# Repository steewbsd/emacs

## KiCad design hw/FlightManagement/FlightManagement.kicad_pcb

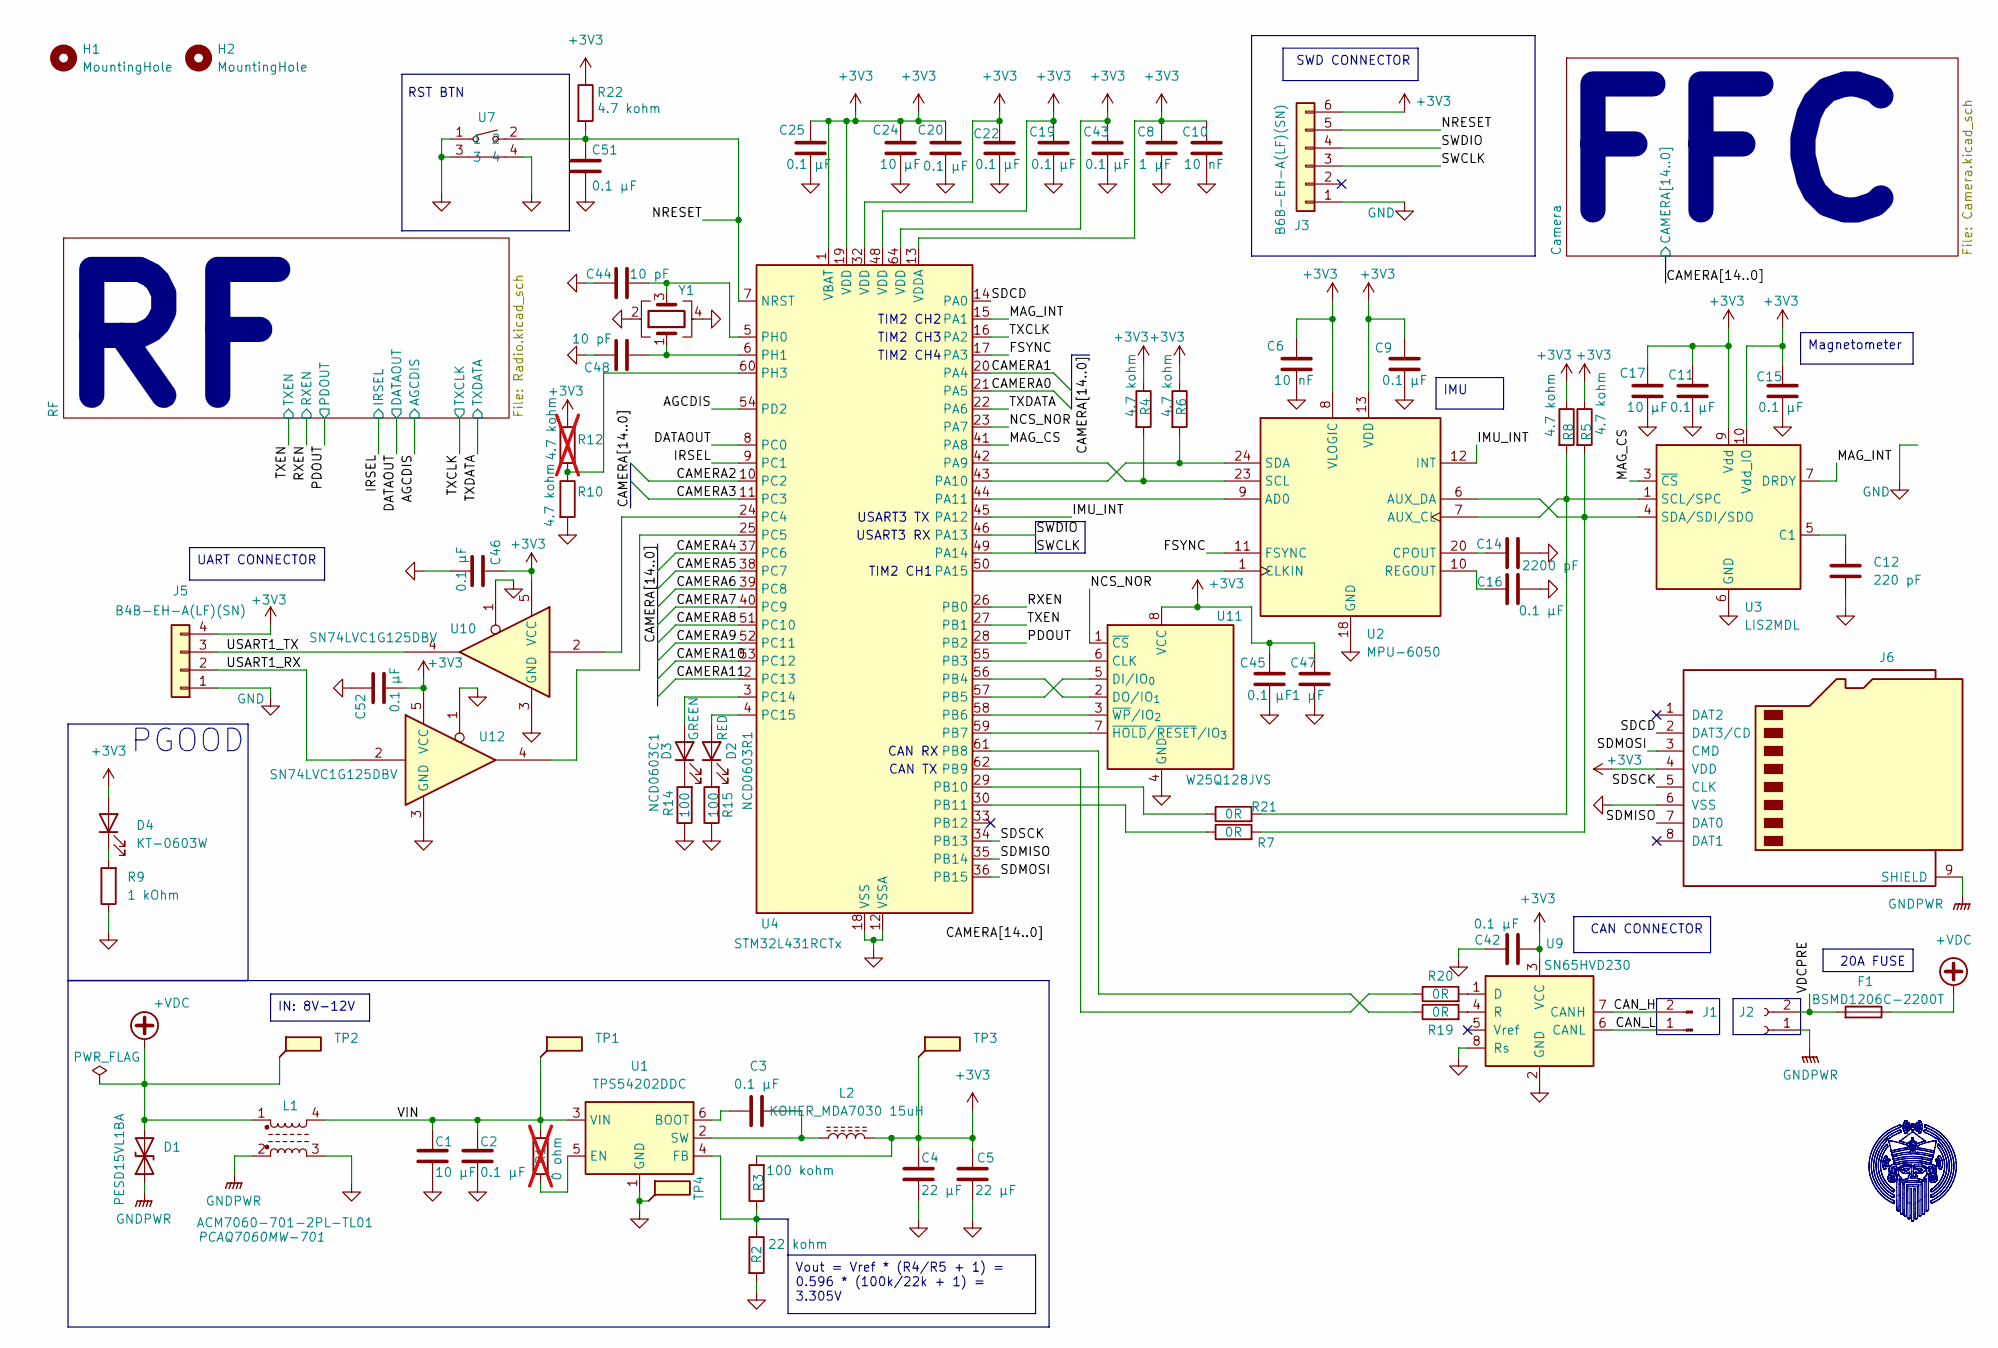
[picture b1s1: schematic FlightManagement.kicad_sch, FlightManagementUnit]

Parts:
C1, C17, C24: 10 µF; C_0603_1608Metric_Pad1.08x0.95mm_HandSolder; Rated Voltage 16V; Tolerance 10%
C2, C3, C9, C11, C15, C16, C19, C20, C22, C25, C42, C43, C45, C46, C51, C52: 0.1 µF; C_0603_1608Metric_Pad1.08x0.95mm_HandSolder; Rated Voltage 50V; Tolerance 10%
C4, C5: 22 µF; C_0603_1608Metric_Pad1.08x0.95mm_HandSolder; Rated Voltage 16V; Tolerance 20%
C6, C10: 10 nF; C_0603_1608Metric_Pad1.08x0.95mm_HandSolder; Rated Voltage 50V; Tolerance 10%
C8, C47: 1 µF; C_0603_1608Metric_Pad1.08x0.95mm_HandSolder; Rated Voltage 25V; Tolerance 10%
C12: 220 pF; C_0603_1608Metric_Pad1.08x0.95mm_HandSolder
C14: 2200 pF; C_0603_1608Metric_Pad1.08x0.95mm_HandSolder
C44, C48: 10 pF; C_0603_1608Metric_Pad1.08x0.95mm_HandSolder; Rated Voltage 50V; Tolerance 0.25pF
D1: PESD15VL1BA; D_SOD-323_HandSoldering
D2: RED; LED_0603_1608Metric
D3: GREEN; LED_0603_1608Metric
D4: KT-0603W; LED_0603_1608Metric_Pad1.05x0.95mm_HandSolder
F1: BSMD1206C-2200T; Fuse_1206_3216Metric_Pad1.42x1.75mm_HandSolder
H1, H2: MountingHole; MountingHole_2.2mm_M2
J1: Conn_01x02_Pin; JST_XH_B2B-XH-A_1x02_P2.50mm_Vertical
J2: Conn_01x02_Socket; JST_VL_B02P-VL_1x02_P6.2mm_Vertical
J3: B6B-EH-A(LF)(SN); JST_EH_B6B-EH-A_1x06_P2.50mm_Vertical
J5: B4B-EH-A(LF)(SN); JST_EH_B4B-EH-A_1x04_P2.50mm_Vertical
J6: Micro_SD_Card; microSD_HC_Molex_47219-2001
L1: L_Ferrite_Coupled_1423; L_CommonModeChoke_TDK_ACM7060
L2: KOHER_MDA7030 15uH; L_KOHERelec_MDA7030
R1: 0 ohm; R_0603_1608Metric_Pad0.98x0.95mm_HandSolder; Tolerance Jumper; not fitted
R2: 22 kohm; R_0603_1608Metric_Pad0.98x0.95mm_HandSolder; Tolerance 1%
R3: 100 kohm; R_0603_1608Metric_Pad0.98x0.95mm_HandSolder; Tolerance 1%
R4, R5, R6, R8, R10, R22: 4.7 kohm; R_0603_1608Metric_Pad0.98x0.95mm_HandSolder; Tolerance 1%
R7, R19, R20, R21: 0R; R_0603_1608Metric_Pad0.98x0.95mm_HandSolder
R9: 1 kOhm; R_0603_1608Metric_Pad0.98x0.95mm_HandSolder
R12: 4.7 kohm; R_0603_1608Metric_Pad0.98x0.95mm_HandSolder; Tolerance 1%; not fitted
R14, R15: 100; R_0603_1608Metric
TP1, TP2, TP3, TP4: TestPoint_Flag; TestPoint_Pad_1.0x1.0mm
U1: TPS54202DDC; SOT-23-6_Handsoldering
U2: MPU-6050; InvenSense_QFN-24_4x4mm_P0.5mm
U3: LIS2MDL; LGA-12_2x2mm_P0.5mm
U4: STM32L431RCTx; LQFP-64_10x10mm_P0.5mm
U7: YTS1C0033BBG01; SW-SMD_YIYUAN_YTS1C003XXX; LCSC Part C5188566
U9: SN65HVD230; SOIC-8_3.9x4.9mm_P1.27mm
U10, U12: SN74LVC1G125DBV; SOT-23-5_HandSoldering
U11: W25Q128JVS; SOIC-8_5.3x5.3mm_P1.27mm
Y1: Crystal_GND24; Crystal_SMD_3225-4Pin_3.2x2.5mm_HandSoldering

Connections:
+3V3: C4.1, C5.1, C6.2, C8.2, C9.2, C10.2, C11.2, C15.2, C17.1, C19.2, C20.2, C22.2, C24.1, C25.2, C42.1, C43.2, C45.2, C46.2, C47.2, C52.1, D4.2 (A), J3.6, J5.4, J6.4 (VDD), L2.2, R3.2, R4.1, R5.1, R6.1, R8.1, R12.1, R22.1, TP3.1, U2.8 (VLOGIC), U2.13 (VDD), U3.9 (Vdd), U3.10 (Vdd_IO), U4.1 (VBAT), U4.9 (PC1), U4.13 (VDDA), U4.19 (VDD), U4.32 (VDD), U4.48 (VDD), U4.64 (VDD), U9.3 (VCC), U10.5 (VCC), U11.8 (VCC), U12.5 (VCC); also elsewhere on the board
+VDC: D1.2 (A2), F1.1, L1.1, TP2.1
/AGCDIS: U4.54 (PD2); also elsewhere on the board
/CAMERA0: U4.21 (PA5)
/CAMERA1: U4.20 (PA4)
/CAMERA2: U4.10 (PC2)
/CAMERA3: U4.11 (PC3)
/CAMERA4: U4.37 (PC6)
/CAMERA5: U4.38 (PC7)
/CAMERA6: U4.39 (PC8)
/CAMERA7: U4.40 (PC9)
/CAMERA8: U4.51 (PC10)
/CAMERA9: U4.52 (PC11)
/CAMERA10: U4.53 (PC12)
/CAMERA11: U4.2 (PC13)
/CAN_H: J1.2, U9.7 (CANH)
/CAN_L: J1.1, U9.6 (CANL)
/DATAOUT: U4.8 (PC0); also elsewhere on the board
/FSYNC: U2.11 (FSYNC), U4.17 (PA3)
/IMU_INT: U2.12 (INT), U4.45 (PA12)
/MAG_CS: U3.3 (~CS), U4.41 (PA8)
/MAG_INT: U3.7 (DRDY), U4.15 (PA1)
/NCS_NOR: U4.23 (PA7), U11.1 (~CS)
/NRESET: C51.1, J3.5, R22.2, U4.7 (NRST), U7.2
/PDOUT: U4.28 (PB2); also elsewhere on the board
/RXEN: U4.26 (PB0); also elsewhere on the board
/SDCD: J6.2 (DAT3/CD), U4.14 (PA0)
/SDMISO: J6.7 (DAT0), U4.35 (PB14)
/SDMOSI: J6.3 (CMD), U4.36 (PB15)
/SDSCK: J6.5 (CLK), U4.34 (PB13)
/SWCLK: J3.3, U4.49 (PA14)
/SWDIO: J3.4, U4.46 (PA13)
/TXCLK: U4.16 (PA2); also elsewhere on the board
/TXDATA: U4.22 (PA6); also elsewhere on the board
/TXEN: U4.27 (PB1); also elsewhere on the board
/USART1_RX: J5.2, U12.2
/USART1_TX: J5.3, U10.4
/VDCPRE: F1.2, J2.2
/VIN: C1.1, C2.1, L1.4, R1.1, TP1.1, U1.3 (VIN)
GND: C1.2, C2.2, C4.2, C5.2, C6.1, C8.1, C9.1, C10.1, C11.1, C12.2, C14.2, C15.1, C16.1, C17.2, C19.1, C20.1, C22.1, C24.2, C25.1, C42.2, C43.1, C44.1, C45.1, C46.1, C47.1, C48.1, C51.2, C52.2, J3.1, J5.1, J6.6 (VSS), L1.3, R2.2, R9.1, R10.2, R14.1, R15.1, TP4.1, U1.1 (GND), U2.18 (GND), U3.6 (GND), U3.8 (GND), U4.12 (VSSA), U4.18 (VSS), U4.31 (VSS), U4.47 (VSS), U4.63 (VSS), U7.1, U7.3, U7.4, U9.2 (GND), U9.8 (Rs), U10.1, U10.3 (GND), U11.4 (GND), U12.1, U12.3 (GND), Y1.2, Y1.4; also elsewhere on the board
GNDPWR: D1.1 (A1), J2.1, J6.9 (SHIELD), L1.2
unnamed: D2.2 (A), U4.4 (PC15)
unnamed: D2.1 (K), R15.2
unnamed: D3.2 (A), U4.3 (PC14)
unnamed: D3.1 (K), R14.2
unnamed: D4.1 (K), R9.2
unnamed: R4.2, U2.23 (SCL), U4.42 (PA9)
unnamed: R6.2, U2.24 (SDA), U4.43 (PA10)
unnamed: U2.9 (AD0), U4.44 (PA11)
unnamed: U2.1 (CLKIN), U4.50 (PA15)
unnamed: U4.55 (PB3), U11.6 (CLK)
unnamed: U4.56 (PB4), U11.2 (DO/IO_{1})
unnamed: U4.57 (PB5), U11.5 (DI/IO_{0})
unnamed: U4.58 (PB6), U11.3 (~WP/IO_{2})
unnamed: U4.59 (PB7), U11.7 (~HOLD/~RESET/IO_{3})
unnamed: R19.1, U4.61 (PB8)
unnamed: R20.1, U4.62 (PB9)
unnamed: R21.1, U4.29 (PB10)
unnamed: R7.1, U4.30 (PB11)
unnamed: U4.24 (PC4), U10.2
unnamed: U4.25 (PC5), U12.4
unnamed: C44.2, U4.5 (PH0), Y1.3
unnamed: C48.2, U4.6 (PH1), Y1.1
unnamed: R10.1, R12.2, U4.60 (PH3)
unnamed: R8.2, R21.2, U2.7 (AUX_CL), U3.1 (SCL/SPC)
unnamed: R5.2, R7.2, U2.6 (AUX_DA), U3.4 (SDA/SDI/SDO)
unnamed: C14.1, U2.20 (CPOUT)
unnamed: C16.2, U2.10 (REGOUT)
unnamed: C12.1, U3.5 (C1)
unnamed: R20.2, U9.1 (D)
unnamed: R19.2, U9.4 (R)
unnamed: C3.1, U1.6 (BOOT)
unnamed: R1.2, U1.5 (EN)
unnamed: R2.1, R3.1, U1.4 (FB)
unnamed: C3.2, L2.1, U1.2 (SW)

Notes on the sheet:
USART3 RX
FFC
RST BTN
PGOOD
TIM2 CH2
USART3 TX
TIM2 CH3
TIM2 CH1
CAN TX
CAN RX
TIM2 CH4
Vout = Vref * (R4/R5 + 1) = 0.596 * (100k/22k + 1) = 3.305V
Magnetometer
IMU
SWD CONNECTOR
UART CONNECTOR
IN: 8V-12V
20A FUSE
CAN CONNECTOR

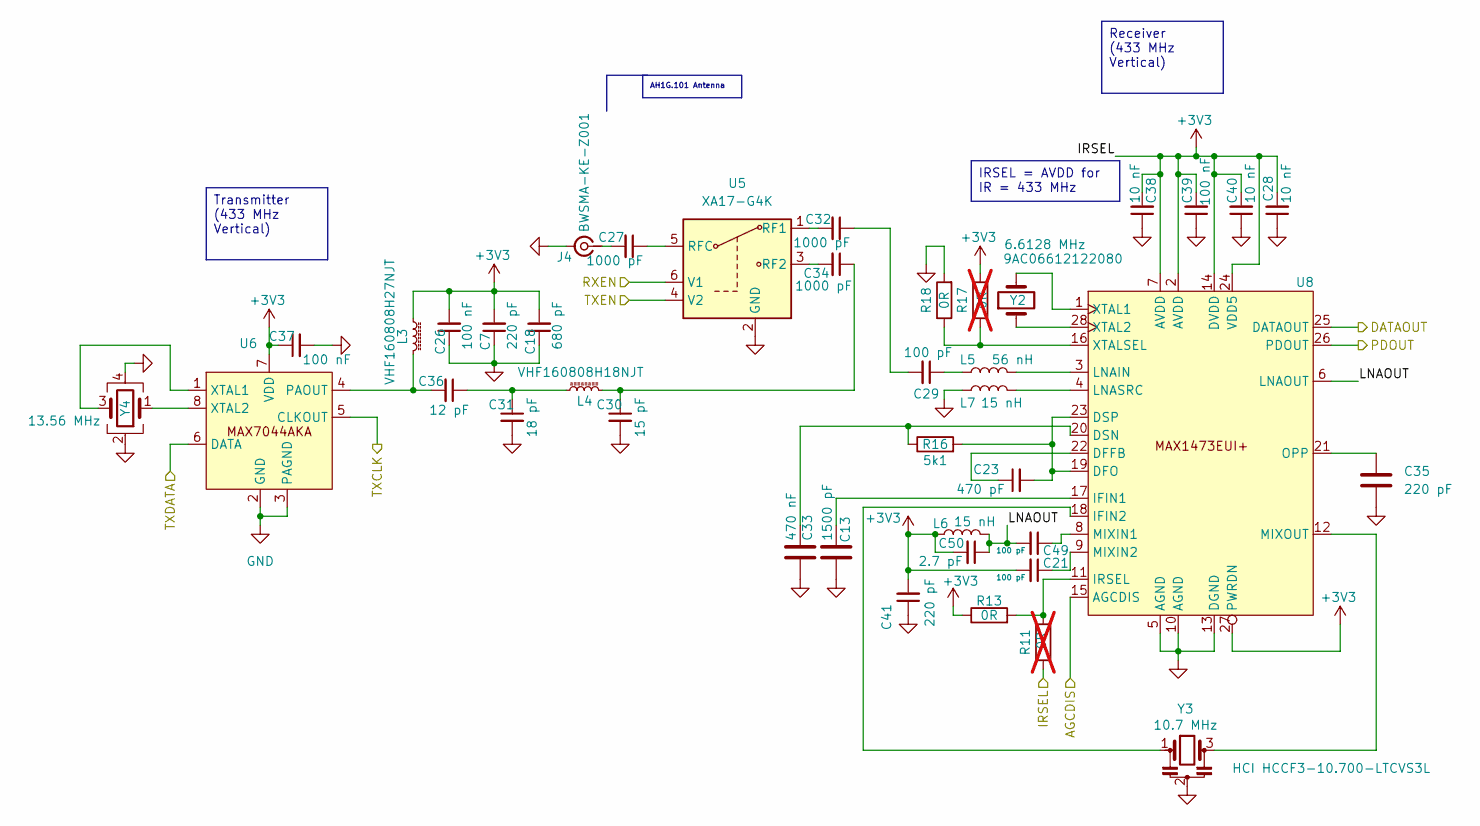
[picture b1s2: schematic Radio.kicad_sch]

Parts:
C7, C35, C41: 220 pF; C_0603_1608Metric_Pad1.08x0.95mm_HandSolder
C13: 1500 pF; C_0603_1608Metric_Pad1.08x0.95mm_HandSolder
C18: 680 pF; C_0603_1608Metric_Pad1.08x0.95mm_HandSolder
C21, C29, C49: 100 pF; C_0603_1608Metric_Pad1.08x0.95mm_HandSolder
C23: 470 pF; C_0603_1608Metric_Pad1.08x0.95mm_HandSolder
C26, C37, C39: 100 nF; C_0603_1608Metric_Pad1.08x0.95mm_HandSolder
C27, C32, C34: 1000 pF; C_0603_1608Metric_Pad1.08x0.95mm_HandSolder
C28, C38, C40: 10 nF; C_0603_1608Metric_Pad1.08x0.95mm_HandSolder
C30: 15 pF; C_0603_1608Metric_Pad1.08x0.95mm_HandSolder
C31: 18 pF; C_0603_1608Metric_Pad1.08x0.95mm_HandSolder
C33: 470 nF; C_0603_1608Metric_Pad1.08x0.95mm_HandSolder
C36: 12 pF; C_0603_1608Metric_Pad1.08x0.95mm_HandSolder
C50: 2.7 pF; C_0603_1608Metric_Pad1.08x0.95mm_HandSolder
J4: BWSMA-KE-Z001; SMB_Jack_Vertical
L3: VHF160808H27NJT; L_0603_1608Metric_Pad1.05x0.95mm_HandSolder
L4: VHF160808H18NJT; L_0603_1608Metric_Pad1.05x0.95mm_HandSolder
L5: 56 nH; L_0603_1608Metric_Pad1.05x0.95mm_HandSolder
L6, L7: 15 nH; L_0603_1608Metric_Pad1.05x0.95mm_HandSolder
R11, R17: 0R; R_0603_1608Metric_Pad0.98x0.95mm_HandSolder; not fitted
R13, R18: 0R; R_0603_1608Metric_Pad0.98x0.95mm_HandSolder
R16: 5k1; R_0603_1608Metric_Pad0.98x0.95mm_HandSolder
U5: XA17-G4K; SOT-363_SC-70-6
U6: MAX7044AKA
U8: MAX1473EUI+
Y2: 6.6128 MHz; Crystal_SMD_HC49-SD
Y3: 10.7 MHz; Resonator_SMD_Murata_SFECV-3Pin_6.9x2.9mm_HandSoldering
Y4: 13.56 MHz; Crystal_SMD_2016-4Pin_2.0x1.6mm

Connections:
+3V3: C7.2, C18.2, C21.2, C26.2, C28.2, C37.1, C38.2, C39.2, C40.2, C41.2, C50.2, L3.1, L6.1, R11.1, R13.1, R17.2, U6.7 (VDD), U8.2 (AVDD), U8.7 (AVDD), U8.14 (DVDD), U8.24 (VDD5), U8.27 (PWRDN); also elsewhere on the board
/AGCDIS: U8.15 (AGCDIS); also elsewhere on the board
/DATAOUT: U8.25 (DATAOUT); also elsewhere on the board
/PDOUT: U8.26 (PDOUT); also elsewhere on the board
/RF/LNAOUT: C49.2, C50.1, L6.2, U8.6 (LNAOUT)
/RXEN: U5.6 (V1); also elsewhere on the board
/TXCLK: U6.5 (CLKOUT); also elsewhere on the board
/TXDATA: U6.6 (DATA); also elsewhere on the board
/TXEN: U5.4 (V2); also elsewhere on the board
GND: C7.1, C13.2, C18.1, C26.1, C28.1, C30.2, C31.2, C33.2, C35.2, C37.2, C38.1, C39.1, C40.1, C41.1, J4.2 (Ext), L7.1, R18.2, U5.2 (GND), U6.2 (GND), U6.3 (PAGND), U8.5 (AGND), U8.10 (AGND), U8.13 (DGND), Y3.2, Y4.2, Y4.4; also elsewhere on the board
unnamed: C31.1, C36.1, L4.1
unnamed: C30.1, C34.1, L4.2
unnamed: C29.2, C32.1
unnamed: C29.1, L5.1
unnamed: C27.2, J4.1 (In)
unnamed: C36.2, L3.2, U6.4 (PAOUT)
unnamed: U6.1 (XTAL1), Y4.3
unnamed: U6.8 (XTAL2), Y4.1
unnamed: C32.2, U5.1 (RF1)
unnamed: C34.2, U5.3 (RF2)
unnamed: C27.1, U5.5 (RFC)
unnamed: C23.1, U8.22 (DFFB)
unnamed: C23.2, R16.2, U8.19 (DFO), U8.23 (DSP)
unnamed: C33.1, R16.1, U8.20 (DSN)
unnamed: C13.1, U8.17 (IFIN1)
unnamed: U8.18 (IFIN2), Y3.1
unnamed: R11.2, R13.2, U8.11 (IRSEL)
unnamed: L5.2, U8.3 (LNAIN)
unnamed: L7.2, U8.4 (LNASRC)
unnamed: C49.1, U8.8 (MIXIN1)
unnamed: C21.1, U8.9 (MIXIN2)
unnamed: U8.12 (MIXOUT), Y3.3
unnamed: C35.1, U8.21 (OPP)
unnamed: U8.1 (XTAL1), Y2.2
unnamed: U8.28 (XTAL2), Y2.1
unnamed: R17.1, R18.1, U8.16 (XTALSEL)

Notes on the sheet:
Receiver (433 MHz Vertical)
AH1G.101 Antenna
Transmitter (433 MHz Vertical)
IRSEL = AVDD for IR = 433 MHz

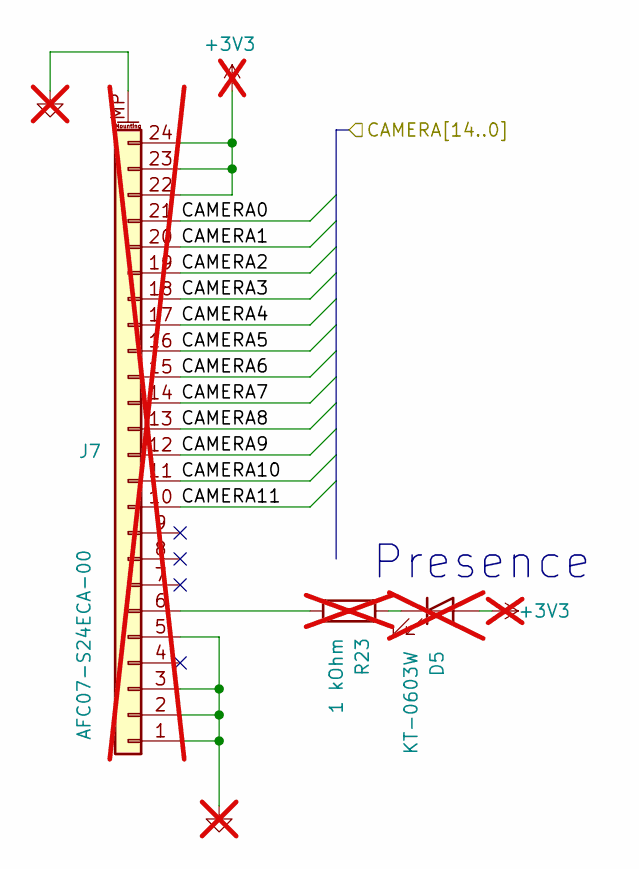
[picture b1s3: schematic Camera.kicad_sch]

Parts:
D5: KT-0603W; LED_0603_1608Metric_Pad1.05x0.95mm_HandSolder; not fitted
J7: Conn_01x24_MountingPin; Jushuo_AFC07-S24FCA-00_1x24-1MP_P0.50_Horizontal; not fitted
R23: 1 kOhm; R_0603_1608Metric_Pad0.98x0.95mm_HandSolder; not fitted

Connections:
unnamed: D5.1 (K), R23.2
unnamed: D5.2 (A), J7.22, J7.23, J7.24
unnamed: J7.1, J7.2, J7.3, J7.5, J7.MP (MountPin)
unnamed: J7.6, R23.1

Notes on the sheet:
Presence

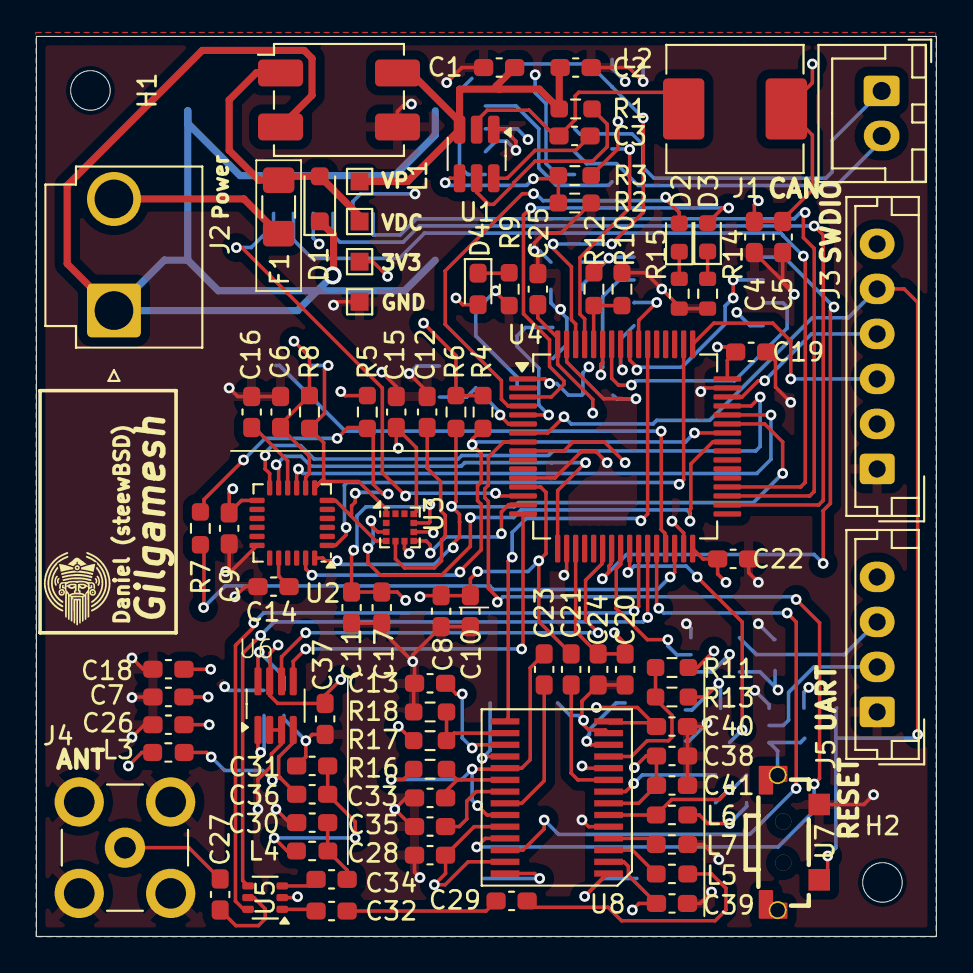
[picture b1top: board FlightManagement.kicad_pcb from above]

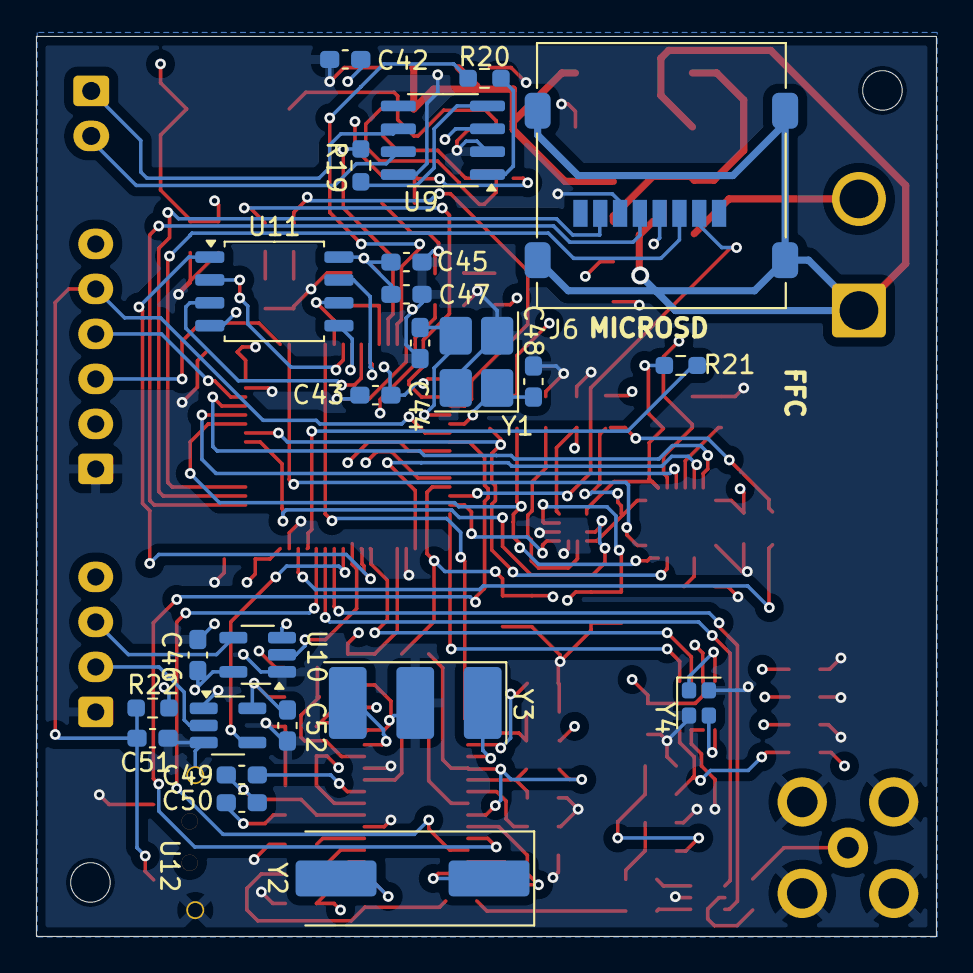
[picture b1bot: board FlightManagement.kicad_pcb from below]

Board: 4 copper layers, 50.0 x 50.0 mm, 114 parts (24 on the bottom side), 90 nets.

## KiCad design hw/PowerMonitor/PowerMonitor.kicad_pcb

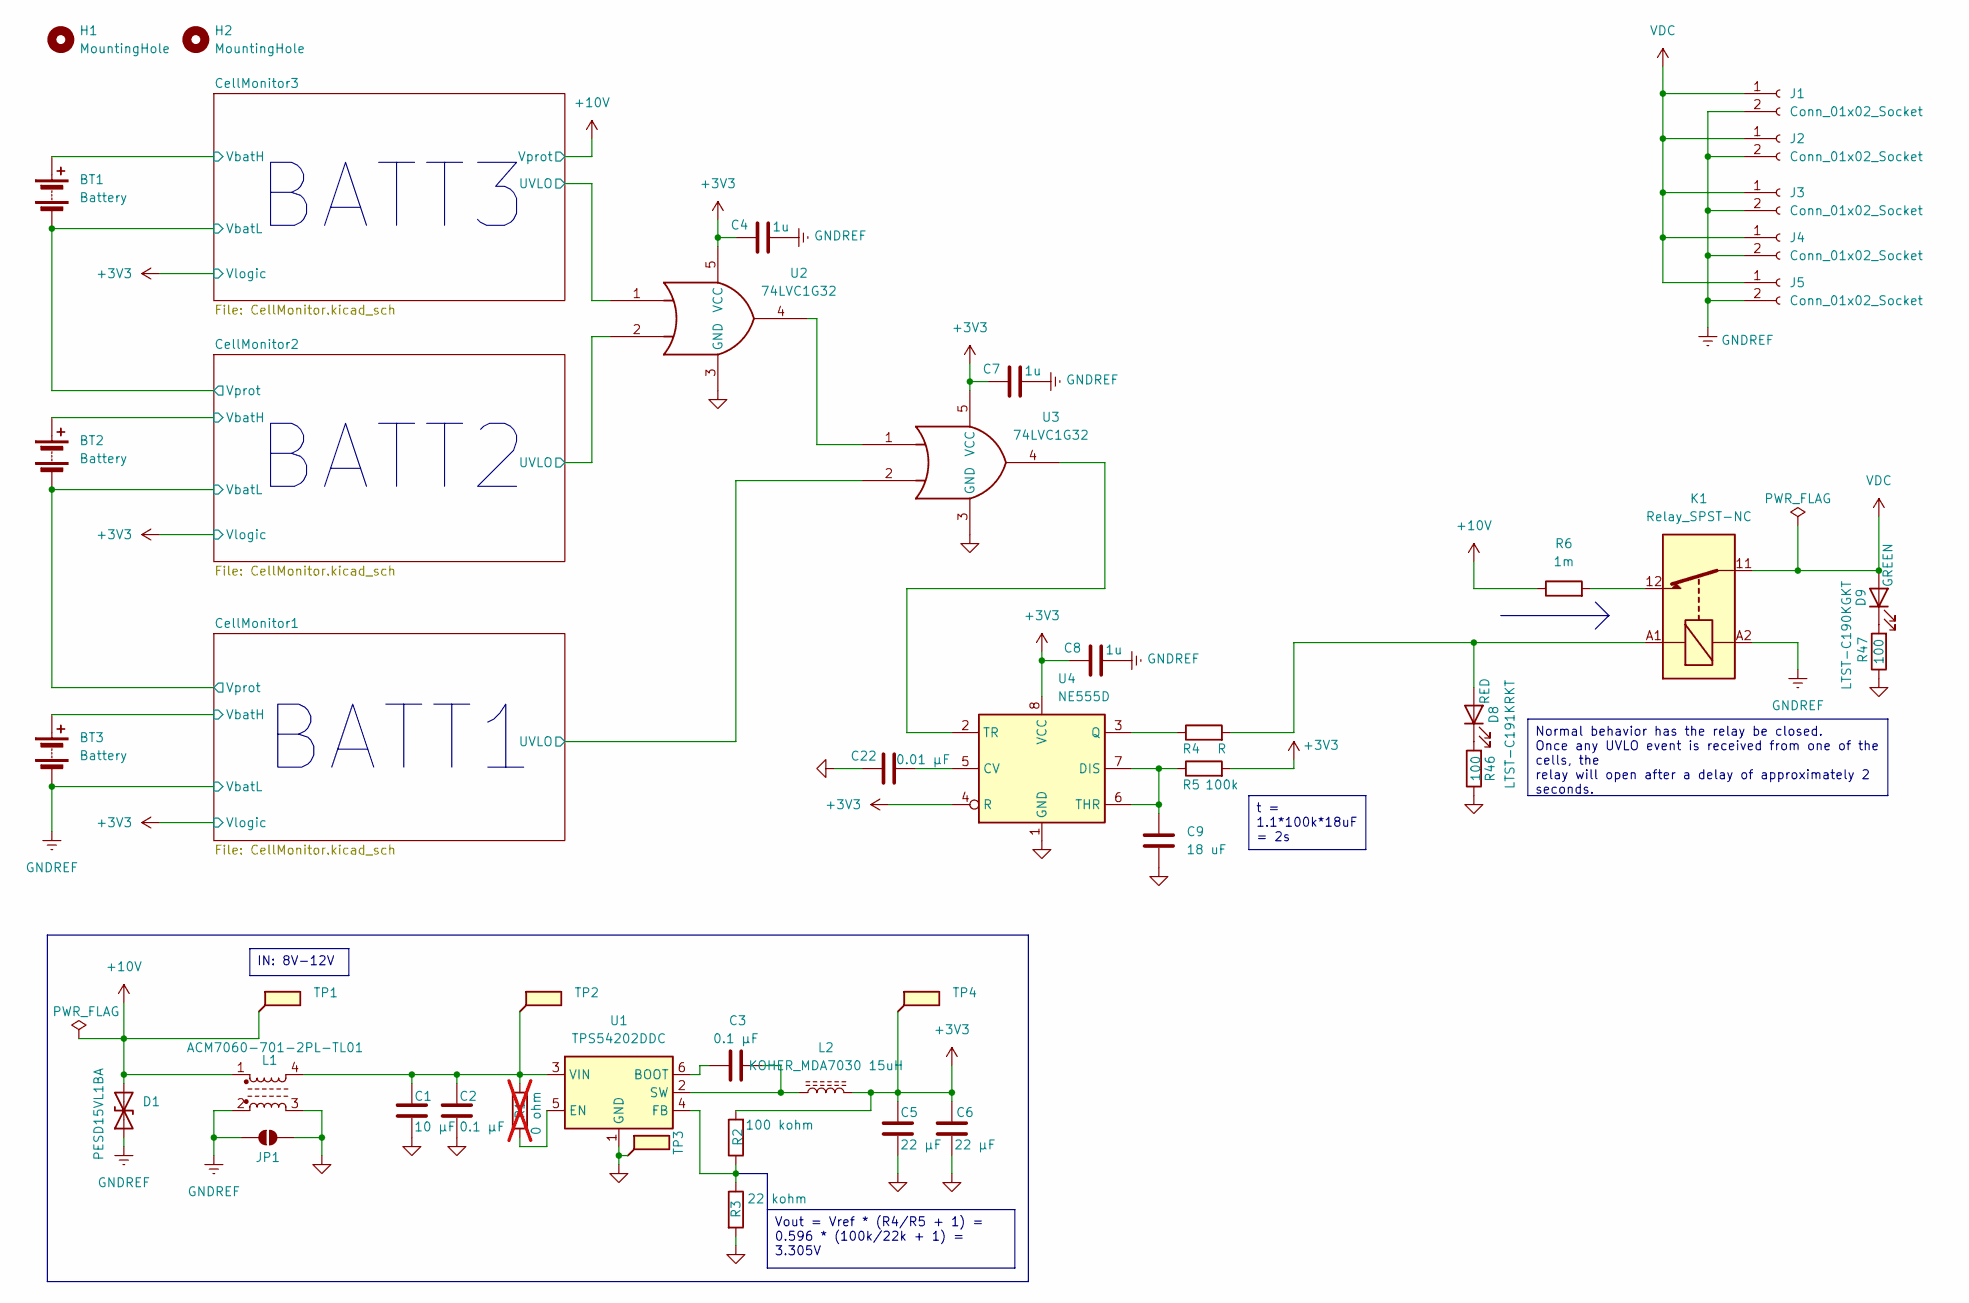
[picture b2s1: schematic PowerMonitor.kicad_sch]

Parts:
BT1, BT2, BT3: Battery; BatteryHolder_Keystone_1042_1x18650
C1: 10 µF; C_0603_1608Metric_Pad1.08x0.95mm_HandSolder; Rated Voltage 16V; Tolerance 10%
C2, C3: 0.1 µF; C_0603_1608Metric_Pad1.08x0.95mm_HandSolder; Rated Voltage 50V; Tolerance 10%
C4, C7, C8: 1u; C_0603_1608Metric_Pad1.08x0.95mm_HandSolder
C5, C6: 22 µF; C_0603_1608Metric_Pad1.08x0.95mm_HandSolder; Rated Voltage 16V; Tolerance 20%
C9: 18 uF; C_0603_1608Metric_Pad1.08x0.95mm_HandSolder
C22: 0.01 µF; C_0603_1608Metric_Pad1.08x0.95mm_HandSolder; Rated Voltage 50V; Tolerance 10%
D1: PESD15VL1BA; D_SOD-323_HandSoldering
D8: RED; LED_0603_1608Metric
D9: GREEN; LED_0603_1608Metric
H1, H2: MountingHole; MountingHole_2.2mm_M2
J1, J2, J3, J4, J5: Conn_01x02_Socket; JST_VL_B02P-VL_1x02_P6.2mm_Vertical
JP1: SolderJumper_2_Open; SolderJumper-2_P1.3mm_Open_RoundedPad1.0x1.5mm
K1: Relay_SPST-NC
L1: L_Ferrite_Coupled_1423; L_CommonModeChoke_TDK_ACM7060
L2: KOHER_MDA7030 15uH; L_KOHERelec_MDA7030
R1: 0 ohm; R_0603_1608Metric_Pad0.98x0.95mm_HandSolder; Tolerance Jumper; not fitted
R2: 100 kohm; R_0603_1608Metric_Pad0.98x0.95mm_HandSolder; Tolerance 1%
R3: 22 kohm; R_0603_1608Metric_Pad0.98x0.95mm_HandSolder; Tolerance 1%
R4: R; R_0603_1608Metric_Pad0.98x0.95mm_HandSolder
R5: 100k; R_0603_1608Metric_Pad0.98x0.95mm_HandSolder
R6: 1m; R_2512_6332Metric_Pad1.40x3.35mm_HandSolder
R46, R47: 100; R_0603_1608Metric
TP1, TP2, TP3, TP4: TestPoint_Flag; TestPoint_Pad_1.0x1.0mm
U1: TPS54202DDC; SOT-23-6_Handsoldering
U2, U3: 74LVC1G32; SOT-353_SC-70-5_Handsoldering
U4: NE555D; SOIC-8_3.9x4.9mm_P1.27mm

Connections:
+3V3: C4.1, C5.1, C6.1, C7.1, C8.1, L2.2, R2.2, R5.2, TP4.1, U2.5 (VCC), U3.5 (VCC), U4.4 (R), U4.8 (VCC); also elsewhere on the board
+10V: D1.2 (A2), L1.1, R6.1, TP1.1; also elsewhere on the board
/CellMonitor1/UVLO: U3.2; also elsewhere on the board
/CellMonitor1/VbatH: BT3.1 (+); also elsewhere on the board
/CellMonitor1/Vprot: BT2.2 (-); also elsewhere on the board
/CellMonitor2/UVLO: U2.2; also elsewhere on the board
/CellMonitor2/VbatH: BT2.1 (+); also elsewhere on the board
/CellMonitor2/Vprot: BT1.2 (-); also elsewhere on the board
/CellMonitor3/UVLO: U2.1; also elsewhere on the board
/CellMonitor3/VbatH: BT1.1 (+); also elsewhere on the board
GND: C1.2, C2.2, C5.2, C6.2, C9.2, C22.1, JP1.2 (B), L1.3, R3.2, R46.1, R47.1, TP3.1, U1.1 (GND), U2.3 (GND), U3.3 (GND), U4.1 (GND); also elsewhere on the board
GNDREF: BT3.2 (-), C4.2, C7.2, C8.2, D1.1 (A1), J1.2, J2.2, J3.2, J4.2, J5.2, JP1.1 (A), K1.A2, L1.2; also elsewhere on the board
unnamed: C22.2, U4.5 (CV)
unnamed: D8.1 (K), R46.2
unnamed: D8.2 (A), K1.A1, R4.2
unnamed: D9.1 (K), R47.2
unnamed: K1.12, R6.2
unnamed: C3.1, U1.6 (BOOT)
unnamed: R1.2, U1.5 (EN)
unnamed: R2.1, R3.1, U1.4 (FB)
unnamed: C3.2, L2.1, U1.2 (SW)
unnamed: C1.1, C2.1, L1.4, R1.1, TP2.1, U1.3 (VIN)
unnamed: U2.4, U3.1
unnamed: C9.1, R5.1, U4.6 (THR), U4.7 (DIS)
unnamed: R4.1, U4.3 (Q)
unnamed: U3.4, U4.2 (TR)
VDC: D9.2 (A), J1.1, J2.1, J3.1, J4.1, J5.1, K1.11

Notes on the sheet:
BATT1
BATT2
BATT3
Normal behavior has the relay be closed. Once any UVLO event is received from one of the cells, the relay will open after a delay of approximately 2 seconds.
t = 1.1*100k*18uF = 2s
Vout = Vref * (R4/R5 + 1) = 0.596 * (100k/22k + 1) = 3.305V
IN: 8V-12V

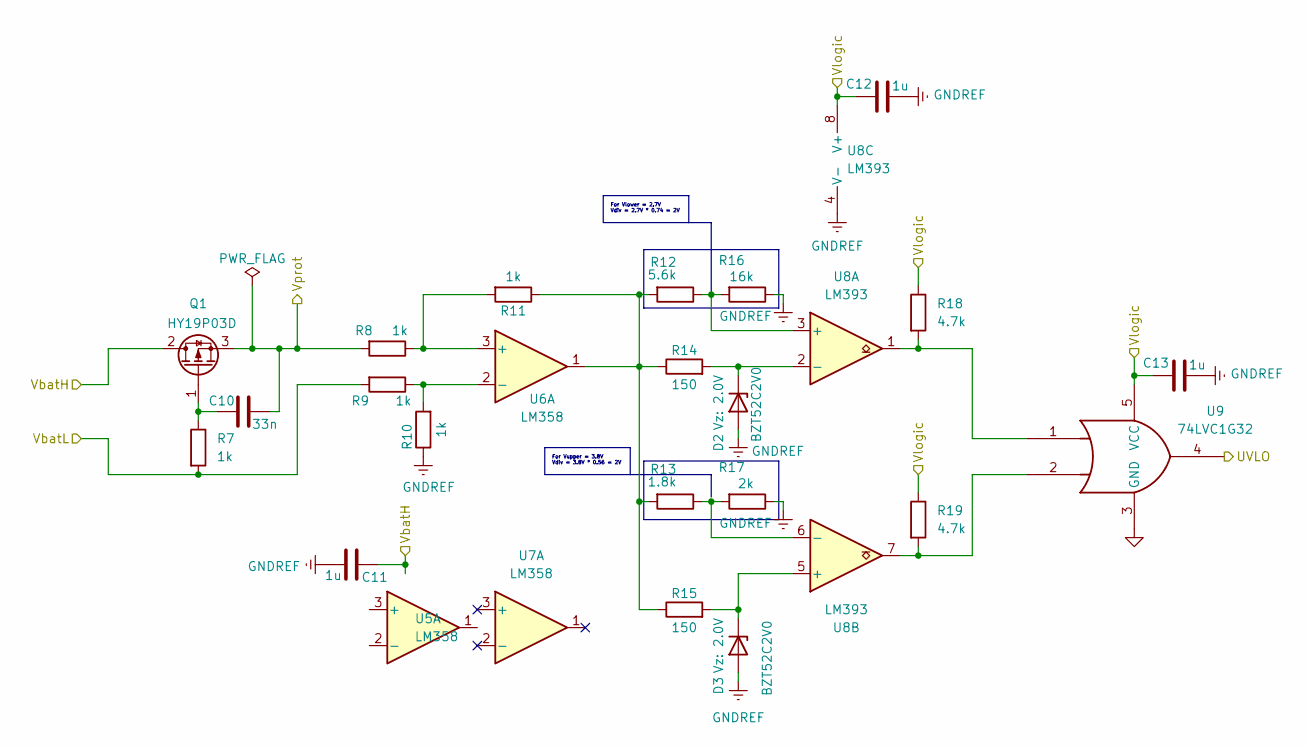
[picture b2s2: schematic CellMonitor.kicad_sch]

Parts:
C10: 33n; C_0603_1608Metric_Pad1.08x0.95mm_HandSolder
C11, C12, C13: 1u; C_0603_1608Metric_Pad1.08x0.95mm_HandSolder
D2, D3: BZT52Bxx; D_SOD-123F
Q1: Q_PMOS_GDS; TO-252-2
R7, R8, R9, R10, R11: 1k; R_0603_1608Metric_Pad0.98x0.95mm_HandSolder
R12: 5.6k; R_0603_1608Metric_Pad0.98x0.95mm_HandSolder
R13: 1.8k; R_0603_1608Metric_Pad0.98x0.95mm_HandSolder
R14, R15: 150; R_0603_1608Metric_Pad0.98x0.95mm_HandSolder
R16: 16k; R_0603_1608Metric_Pad0.98x0.95mm_HandSolder
R17: 2k; R_0603_1608Metric_Pad0.98x0.95mm_HandSolder
R18, R19: 4.7k; R_0603_1608Metric_Pad0.98x0.95mm_HandSolder
U5, U6, U7: LM358; SOIC-8_3.9x4.9mm_P1.27mm
U8: LM393; SOIC-8_3.9x4.9mm_P1.27mm
U9: 74LVC1G32; SOT-353_SC-70-5_Handsoldering

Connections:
+3V3: C12.1, C13.1, R18.1, R19.1, U8.8 (V+), U9.5 (VCC); also elsewhere on the board
/CellMonitor1/UVLO: U9.4; also elsewhere on the board
/CellMonitor1/VbatH: C11.1, Q1.2 (D); also elsewhere on the board
/CellMonitor1/Vprot: C10.2, Q1.3 (S), R8.2; also elsewhere on the board
GND: U9.3 (GND); also elsewhere on the board
GNDREF: C11.2, C12.2, C13.2, D2.2 (A), D3.2 (A), R7.2, R9.2, R10.1, R16.1, R17.1, U8.4 (V-); also elsewhere on the board
unnamed: D2.1 (K), R14.2, U8.2 (-)
unnamed: D3.1 (K), R15.2, U8.5 (+)
unnamed: C10.1, Q1.1 (G), R7.1
unnamed: R11.1, R12.2, R13.2, R14.1, R15.1, U6.1
unnamed: R18.2, U8.1, U9.1
unnamed: R19.2, U8.7, U9.2
unnamed: R8.1, R11.2, U6.3 (+)
unnamed: R9.1, R10.2, U6.2 (-)
unnamed: R12.1, R16.2, U8.3 (+)
unnamed: R13.1, R17.2, U8.6 (-)

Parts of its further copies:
C14, C18: 33n; C_0603_1608Metric_Pad1.08x0.95mm_HandSolder
C15, C16, C17, C19, C20, C21: 1u; C_0603_1608Metric_Pad1.08x0.95mm_HandSolder
D4, D5, D6, D7: BZT52Bxx; D_SOD-123F
Q2, Q3: Q_PMOS_GDS; TO-252-2
R20, R21, R22, R23, R24, R33, R34, R35, R36, R37: 1k; R_0603_1608Metric_Pad0.98x0.95mm_HandSolder
R25, R38: 5.6k; R_0603_1608Metric_Pad0.98x0.95mm_HandSolder
R26, R39: 1.8k; R_0603_1608Metric_Pad0.98x0.95mm_HandSolder
R27, R28, R40, R41: 150; R_0603_1608Metric_Pad0.98x0.95mm_HandSolder
R29, R42: 16k; R_0603_1608Metric_Pad0.98x0.95mm_HandSolder
R30, R43: 2k; R_0603_1608Metric_Pad0.98x0.95mm_HandSolder
R31, R32, R44, R45: 4.7k; R_0603_1608Metric_Pad0.98x0.95mm_HandSolder
U10, U13: LM358; SOIC-8_3.9x4.9mm_P1.27mm
U11, U14: LM393; SOIC-8_3.9x4.9mm_P1.27mm
U12, U15: 74LVC1G32; SOT-353_SC-70-5_Handsoldering

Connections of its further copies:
+3V3: C16.1, C17.1, C20.1, C21.1, R31.1, R32.1, R44.1, R45.1, U11.8 (V+), U12.5 (VCC), U14.8 (V+), U15.5 (VCC); also elsewhere on the board
+10V: C18.2, Q3.3 (S), R34.2; also elsewhere on the board
/CellMonitor1/Vprot: R20.2, R22.2; also elsewhere on the board
/CellMonitor2/UVLO: U12.4; also elsewhere on the board
/CellMonitor2/VbatH: C15.1, Q2.2 (D), U10.8 (V+); also elsewhere on the board
/CellMonitor2/Vprot: C14.2, Q2.3 (S), R21.2, R33.2, R35.2; also elsewhere on the board
/CellMonitor3/UVLO: U15.4; also elsewhere on the board
/CellMonitor3/VbatH: C19.1, Q3.2 (D), U13.8 (V+); also elsewhere on the board
GND: U12.3 (GND), U15.3 (GND); also elsewhere on the board
GNDREF: C15.2, C16.2, C17.2, C19.2, C20.2, C21.2, D4.2 (A), D5.2 (A), D6.2 (A), D7.2 (A), R23.1, R29.1, R30.1, R36.1, R42.1, R43.1, U11.4 (V-), U14.4 (V-); also elsewhere on the board
unnamed: D4.1 (K), R27.2, U11.2 (-)
unnamed: D5.1 (K), R28.2, U11.5 (+)
unnamed: D6.1 (K), R40.2, U14.2 (-)
unnamed: D7.1 (K), R41.2, U14.5 (+)
unnamed: C14.1, Q2.1 (G), R20.1
unnamed: C18.1, Q3.1 (G), R33.1
unnamed: R24.1, R25.2, R26.2, R27.1, R28.1, U10.1
unnamed: R31.2, U11.1, U12.1
unnamed: R32.2, U11.7, U12.2
unnamed: R37.1, R38.2, R39.2, R40.1, R41.1, U13.1
unnamed: R44.2, U14.1, U15.1
unnamed: R45.2, U14.7, U15.2
unnamed: R21.1, R24.2, U10.3 (+)
unnamed: R22.1, R23.2, U10.2 (-)
unnamed: R25.1, R29.2, U11.3 (+)
unnamed: R26.1, R30.2, U11.6 (-)
unnamed: R34.1, R37.2, U13.3 (+)
unnamed: R35.1, R36.2, U13.2 (-)
unnamed: R38.1, R42.2, U14.3 (+)
unnamed: R39.1, R43.2, U14.6 (-)

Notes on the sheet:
For Vlower = 2.7V Vdiv = 2.7V * 0.74 = 2V
For Vupper = 3.8V Vdiv = 3.8V * 0.56 = 2V

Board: 2 copper layers, 108 parts (3 on the bottom side), 52 nets, no tracks yet.
